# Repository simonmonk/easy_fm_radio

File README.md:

# Easy FM Radio

The design files and firmware for my project to build an FM broadcast receiver with the design goals of bing easy to use for someone with dementia or limited dexterity.

At present, there is just a design for a PCB FM Antenna copied from this [research publication](https://www.researchgate.net/publication/277016433_A_Compact_Printed_Spiral_FM_Antenna)

Good instructions and code here for [getting the RDA5807M FM Receiver working with Arduino.](https://www.instructables.com/Arduino-Based-Digital-Audio-FM-Radio-Using-RDA5807/)

You can follow on with the development of this project and find more explanation at the links below.

[Accessible FM Radio Case Study - Part 1](https://www.doctormonk.com/2025/04/accessible-fm-radio-case-study-part-1.html)
[Accessible FM Radio Case Study - Part 2](https://www.doctormonk.com/2025/04/accessible-fm-radio-case-study-part-2.html)

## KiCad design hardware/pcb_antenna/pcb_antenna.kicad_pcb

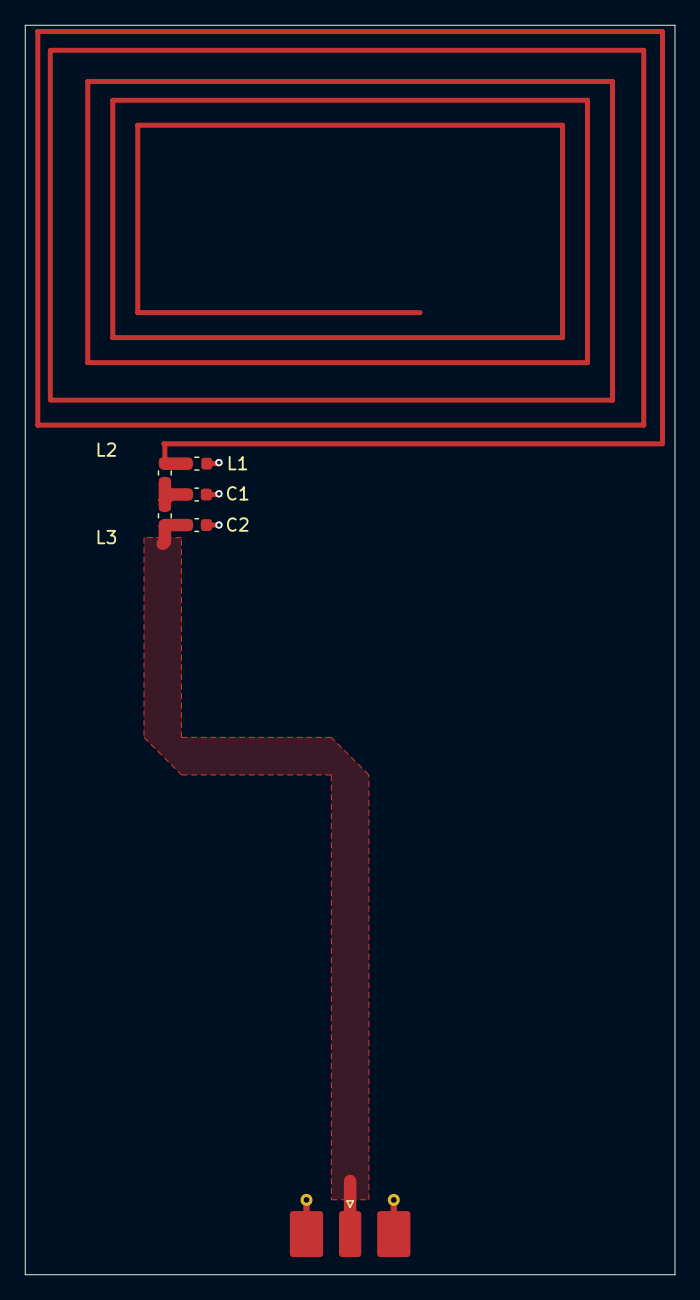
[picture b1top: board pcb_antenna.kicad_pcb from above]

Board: 2 copper layers, 52.0 x 100.0 mm, 6 parts (0 on the bottom side), 4 nets.

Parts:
C1: 82pF; C_0603_1608Metric
C2: 68pF; C_0603_1608Metric
J1: Conn_Coaxial_Small; SMA_Molex_73251-2120_EdgeMount_Horizontal
L1: 68nH; L_0603_1608Metric
L2: 1.5nH; L_0603_1608Metric
L3: 100nH; L_0603_1608Metric

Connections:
GND: C1.2, C2.2, J1.2 (Ext), L1.2
unnamed: L1.1, L2.2
unnamed: C1.1, L2.1, L3.2
OUT: C2.1, J1.1 (In), L3.1

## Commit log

2025-03-27 added cad files
2025-04-12 added Arduino test program
2025-04-15 added to readme
